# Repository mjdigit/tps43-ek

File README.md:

# tps43-ek
Experiment kit of Azoteq TPS43 for study in advance of designing [Girasole40](https://github.com/mjdigit/Girasole40).

## Parts List (WIP)
(In study)

### Parts need to be prepared/purchased
|Part|Quantity|Where I bought it|Remarks|
|---|---|---|---|
|Wired controller board|1|AliExpress|RP2040-Zero (w/ pin headers)|
|Choc socket|4|yushakobo|e.g. Kailh PG1350 KeySwitches Contact (CPG135001S30)|
|Choc V2 switch|4|AliExpress|-|
|Keycap|4|AliExpress|-|
|Touchpad Module TPS43|1|MOUSER|-|
|Polycarbonate sheet for touchpad (0.5mm thickness) <br/>or<br/> PVC sheet for touchpad (0.5mm thikness)|1|Amazon|Need to be cut to suit TPS43|
|PET double-sided adhesive sheet|1|Amazon|Need to be cut to suit TPS43|
|M2 Spacer (3.5mm)|4|yushakobo|-|
|M2 Spacer (5.0mm)|4|yushakobo|-|
|M2 screw (3.5mm)|16|yushakobo|-|
|FPC cable (6pin, 0.5mm pitch, 50mm length)|1|Amazon|-|
|Diode|4|MOUSER|1N4148W|
|Resister 1608 1Kohm|2|akizukidenshi|-|
|Capaciter 1608 10uF|1|akizukidenshi|-|
|FPC socket (6pin, 0.5mm pitch)|1|Amazon|-|
|Rubber feet|5|Amazon|-|

### Parts need to be ordered/printed
|Part|Quantity|Remarks|
|---|---|---|
|Touchpad mount plate|1|<image src="images/TouchpadMountPlate.png" height="100px"/><br>gerber/gerber-touchpad.zip|
|Top plate|1|<image src="images/TopPlate.png" height="100px"/><br>gerber/gerber-top.zip|
|Main plate|1|<image src="images/MainPlate.png" height="100px"/><br>gerber/gerber.zip|
|Bottom plate|1|<image src="images/BottomPlate.png" height="100px"/><br>gerber/gerber-bottom.zip|

## Build Guide (WIP)
### !!! Important Notice !!!
Since I had placed SCL on pin0 and SDA on pin1, which assignment does not work on RP2040-Zero I2C0, some hand bridging is required.
There is no plan to be fix the gerber because this tps-43ek is just experimental project towards Girasole40.

### Assemble passive components on main plate
#### Front side
Solder FPC socket on the main plate.

It's better to check resistance between the pads on main plate and TPS43 with connecting each other to check it successfully soldered.

Solder resisters and a capacitor on front side of the main plate.

#### Back side
Solder diodes then switch sockets on back side of the main plate.

#### RP2040-Zero
Put pin headers then put RP2040-Zero on front side (DO NOT solder yet). 

Solder the pin headers on back side.

Put off RP2040-Zero then remove yellow plastic parts.

Put RP2040-Zero again and solder it. Then cutoff the pins on Front side and Back side using nipper.

#### Work Around: Replace SCL and SDA
As written on "Important Notice", it is required to place SDA on pin0 and SCL on pin1. Please connect each other in the below pads the cutoff the wire towards FPC connector.

#### Check whether touchpad works
Connect the main plate and TPS43 using FPC connector.

Connect your PC to RP2040-Zero with pushing BOOT switch. RP2040-Zero will be recognized as mass strage "RPI-RP2". Put the .uf2 file build by the following instruction into it.

Touch TPS43 and check whether touchpad works.

### Assemble the touchpad
Cut PET double-sided adhesive sheet to suit TPS43.

Adhere Polycarbonate sheet on TPS43 then cut it to suit TPS43.

Put double-sided tape on inside on dashed line of the Touchpad mount plate.

Then, put the plate onto TPS43.

Note that you can also use PVC sheet instead of Polycarbonate sheet, though I feel touch experience is better on Polycarbonate sheet.

### Assemble plates
Put top plate on the main plate. Then put keyboard switches.

Connect the touchpad plate and the main plate with FPC cable.

Then put the touchpad plate on the main plate using 3.5mm spacers and screws.

Put the plates on bottom plate using spacers and screws. And put keycaps.

Finally, put rubber feets on the bottom plate.

## Default layout

You can rotate touchpad and keys using rotate layer.

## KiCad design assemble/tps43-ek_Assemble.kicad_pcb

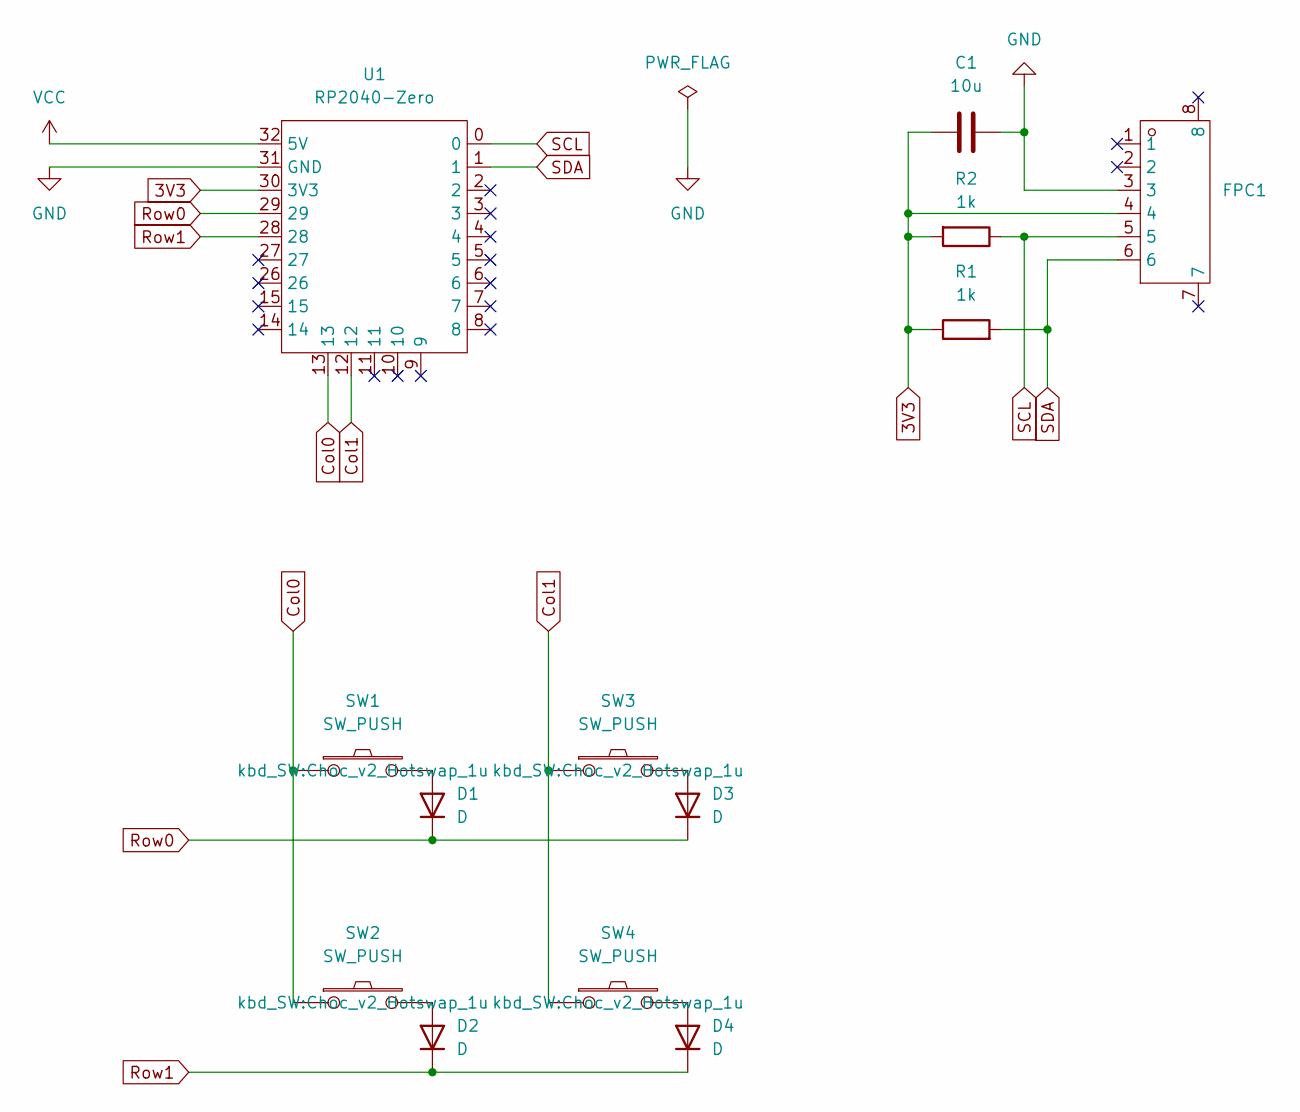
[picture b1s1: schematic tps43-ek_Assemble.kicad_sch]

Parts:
C1: 10u; C_0603_1608Metric_Pad1.08x0.95mm_HandSolder
D1, D2, D3, D4: D; Diode_TH_SMD
FPC1: FPC-6p-P0.5mm; Manufacturer Part FPC-05F-6PH20; LCSC Part Name 翻盖式 卧贴 P数:6P 间距:0.5mm
R1, R2: 1k; R_0603_1608Metric_Pad0.98x0.95mm_HandSolder
SW1, SW2, SW3, SW4: SW_PUSH; Choc_v2_Hotswap_1u
U1: RP2040-Zero

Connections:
3V3: C1.1, FPC1.4, R1.1, R2.2, U1.30 (3V3)
Col0: SW1.1, SW2.1, U1.13
Col1: SW3.1, SW4.1, U1.12
GND: C1.2, FPC1.3, U1.31 (GND)
unnamed: D1.2 (A), SW1.2
unnamed: D2.2 (A), SW2.2
unnamed: D3.2 (A), SW3.2
unnamed: D4.2 (A), SW4.2
Row0: D1.1 (K), D3.1 (K), U1.29
Row1: D2.1 (K), D4.1 (K), U1.28
SCL: FPC1.5, R2.1, U1.0
SDA: FPC1.6, R1.2, U1.1
VCC: U1.32 (5V)

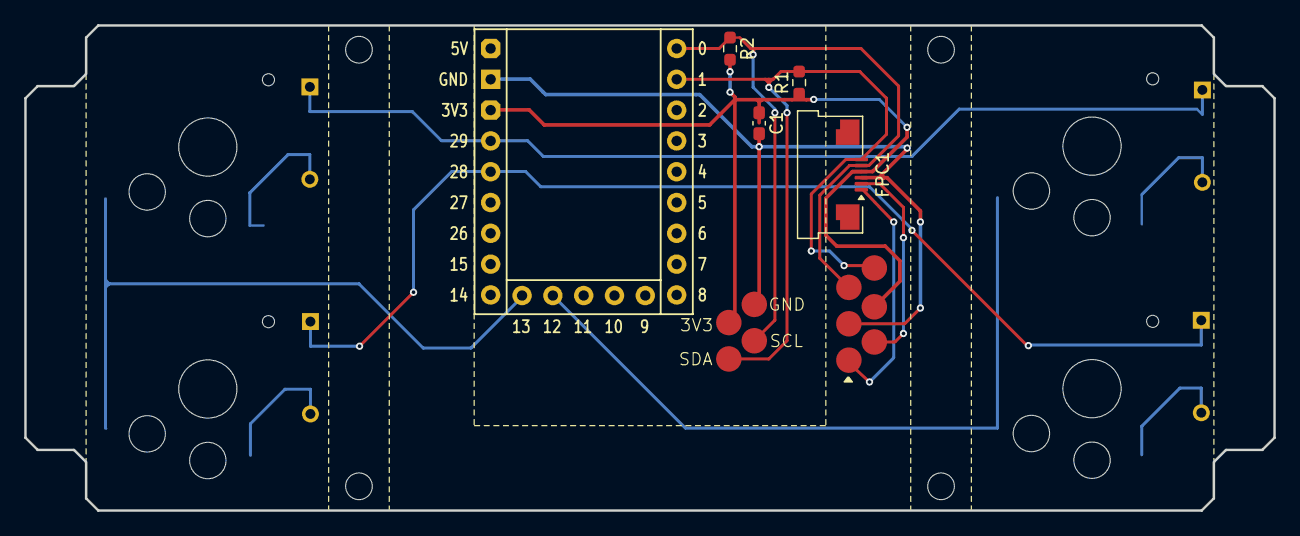
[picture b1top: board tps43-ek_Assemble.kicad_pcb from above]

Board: 2 copper layers, 103.0 x 40.0 mm, 17 parts (0 on the bottom side), 12 nets.

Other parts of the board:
Ref**: M2_ScrewHole
Ref**#2, Ref**#3, Ref**#4: M2_ScrewHole

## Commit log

2025-11-24 Assembling 2025-11-23
2025-11-24 Assemble 2025-11-24_01
2025-11-30 20251130
2025-12-02 2025-12-02
2025-12-03 progress 2025-12-03
2025-12-05 progress 2025-12-04
2025-12-05 Add KiCad assemble files and garber files of a trial design.
2025-12-13 Added a build guide.
2025-12-13 Added assemble files and preliminaly build guide. (#2)
2025-12-27 Making QMK firmware. Touchpad is not working yet.
2025-12-27 Making QMK firmware. Touchpad works with swapping SCL & SCA, but, need some more adjustment.
2026-01-01 Renewed assemble instruction on README.md
2026-01-01 Renewed assemble instruction on README.md (#3)
2026-01-01 Added the pictures into the workaround on README.md
2026-01-01 adjusting scrolling
    Updates Readme
    Update Readme.md
2026-01-02 Added drag-scroll & rotate functionality
2026-01-02 Added key rotation
2026-01-02 Added default keymap for QMK firmware. (#4)
